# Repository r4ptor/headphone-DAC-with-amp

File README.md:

# Portable headphone DAC with amplifier stage

A simple and portable audio digital to analogue converter with amplifying abilities.

## Structure

The Texas Instruments PCM2707 serves as the USB interface. This interface provides a clock and I2S signal for the main Hifi
digital to analogue converter, the PCM1794A.

Since this converter needs a 3.3V power source a LP5907 ultra-low-noise LDO is being used to
generate the desired voltage.

The DAC provides a differential output current. This is being feeded into a two opamps that are used as transimpedance amplifiers which convert the DAC output current into a differential voltage. Then a difference amplifier converts this differential voltage to single-ended. For this the TI reference design [TIDU672C](http://www.ti.com/litv/pdf/tidu672c) was used. Therefore the Amplifier stage consists as two OPA1612 and a OPA1622.

A LM2662M switched capacitor voltage converter generates the necessary -5V to supply the operational amplifiers with +-5V.

The project is realized with the open source EDA tool [KiCad](https://kicad-pcb.org/).

With the current parts the whole project costs around 45€ at [Digikey](https://www.digikey.com/). For details have a look at the [BOM.csv](https://github.com/r4ptor/headphone-DAC-with-amp/blob/master/BOM.csv) or [BOM.html](https://github.com/r4ptor/headphone-DAC-with-amp/blob/master/BOM.html).

## Datasheets of used components
[PCM2707](https://www.ti.com/lit/ds/symlink/pcm2706.pdf) USB Interface

[PCM1794A](http://www.ti.com/lit/ds/symlink/pcm1794a.pdf) 24-Bit, 192-kHz audio DAC

[LP5907](http://www.ti.com/lit/ds/symlink/lp5907.pdf) Low-noise LDO

[LM2662M](http://www.ti.com/lit/ds/symlink/lm2662.pdf) Voltage converter

[OPA1612](http://www.ti.com/lit/ds/symlink/opa1612.pdf) Operational amplifier

[OPA1622](http://www.ti.com/lit/ds/symlink/opa1622.pdf) Operational amplifier

## Rendered picture of the current PCB layout

Note: old design!

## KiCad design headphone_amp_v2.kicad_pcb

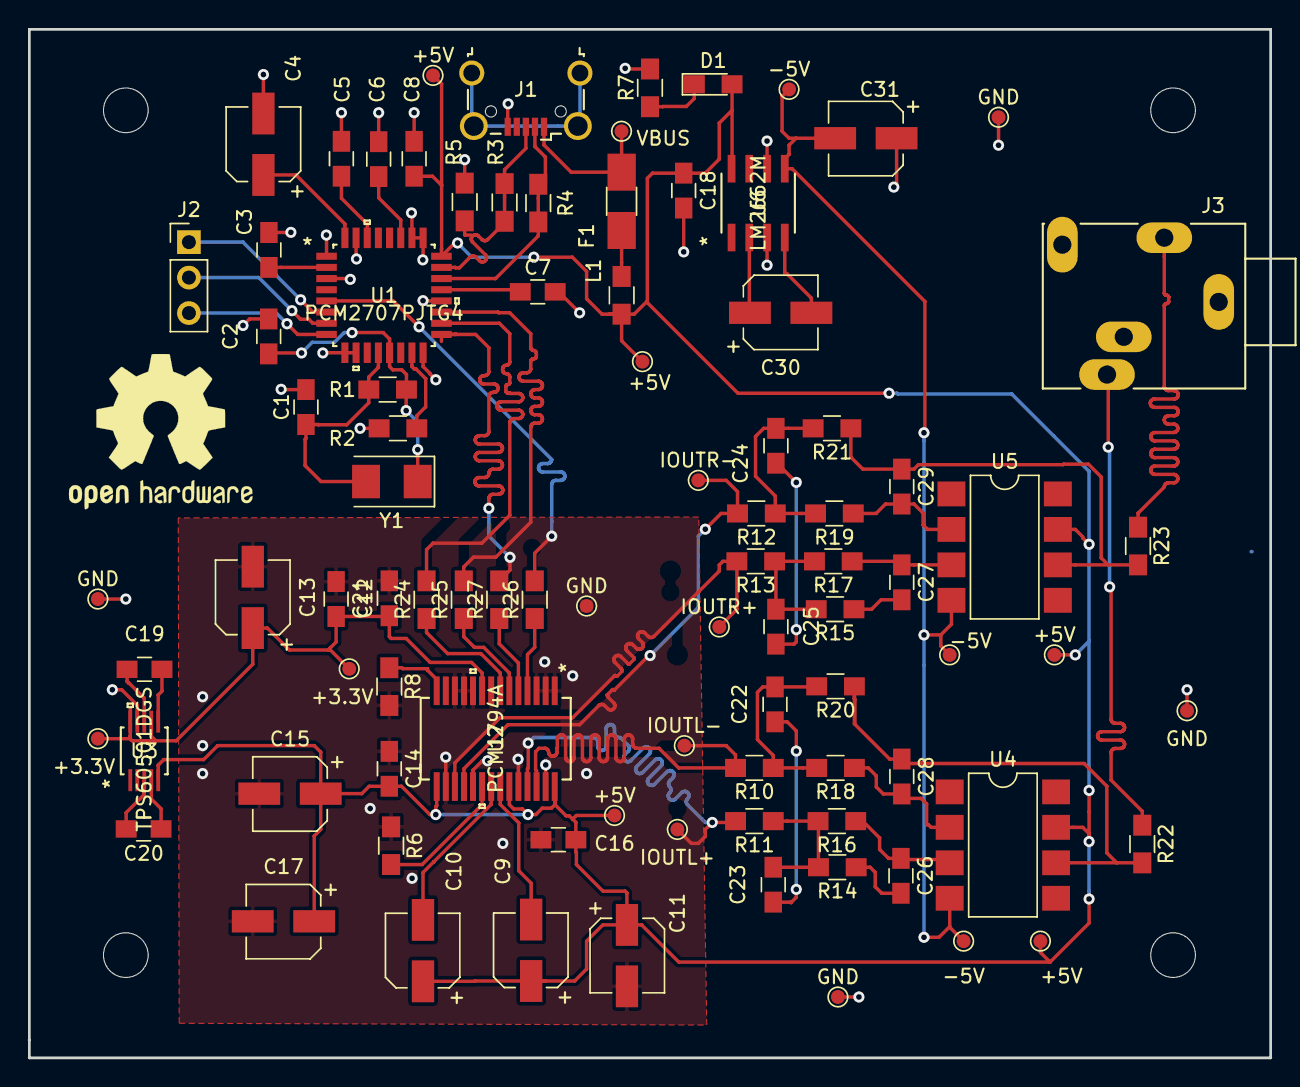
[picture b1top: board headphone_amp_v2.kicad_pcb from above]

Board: 2 copper layers, 88.9 x 73.7 mm, 90 parts (0 on the bottom side), 58 nets.

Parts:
+3.3V, +3.3V#2, +5V, +5V#2, +5V#3, +5V#4, +5V#5: TestPoint_Pad_D1.0mm
-5V, -5V#2, -5V#3: TestPoint_Pad_D1.0mm
C1, C2: 22pF; C_0805_HandSoldering
C3, C5, C6, C7, C8, C19, C20: 1uF; C_0805_HandSoldering
C4, C13: 10uF; CP_Elec_5x5.8
C9, C10, C30, C31: 47uF; CP_Elec_5x5.3
C11, C15, C17: 10uF; CP_Elec_5x5.3
C12, C14, C16: 0.1uF; C_0805_HandSoldering
C18: 2.2uF; C_0805_HandSoldering
C21: 10uF; C_0805_HandSoldering
C22, C23, C24, C25: 4.7nF; C_0805_HandSoldering
C26, C27, C28, C29: 1nF; C_0805_HandSoldering
D1: LED blue; LED_0805_HandSoldering
F1: Polyfuse; Fuse_SMD1206_HandSoldering
GND: TestPoint_Pad_D1.0mm
GND#2, GND#3, GND#4, GND#5: TestPoint_Pad_D1.0mm
IOUTL+: TestPoint_Pad_D1.0mm
IOUTL-: TestPoint_Pad_D1.0mm
IOUTR+: TestPoint_Pad_D1.0mm
IOUTR-: TestPoint_Pad_D1.0mm
J1: USB_OTG; USB_Micro-B_Wuerth-629105150521_CircularHoles
J2: HID_JMP; Pin_Header_Straight_1x03_Pitch2.54mm
J3: AudioJack3_Ground; Stereo_Jack_3.5mm_Switch_Ledino_KB3SPRS
L1: 1A; L_0805_HandSoldering
R1: 1M; R_0805_HandSoldering
R2, R5: 1.5k; R_0805_HandSoldering
R3, R4, R22, R23: 22R; R_0805_HandSoldering
R6, R8: 10k; R_0805_HandSoldering
R7: 560R; R_0805_HandSoldering
R10, R11, R12, R13, R14, R15, R20, R21: 887R; R_0805_HandSoldering
R16, R17, R18, R19: 1.02k; R_0805_HandSoldering
R24, R25, R26: 10R; R_0805_HandSoldering
R27: 47R; R_0805_HandSoldering
U1: PCM2707PJTG4
U2: PCM1794A; PCM1794ADBG4
U3: TPS60501DGS; TPS60501DGSG4
U4, U5: OPA2134PA; SMDIP-8_W7.62mm
U6: LM2662M
VBUS: TestPoint_Pad_D1.0mm
Y1: 12Mhz; Crystal_SMD_5032-2pin_5.0x3.2mm

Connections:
3.3V: +3.3V.1, +3.3V#2.1, C12.1, C13.1, C21.2, U2.9, U3.7, U3.10
5V: +5V.1, +5V#2.1, +5V#3.1, +5V#4.1, +5V#5.1, C8.2, C9.1, C10.1, C11.1, C14.2, C15.1, C16.2, C17.1, C18.1, D1.2, L1.2, U1.24, U2.15, U2.23, U2.28, U3.5, U4.7, U5.7, U6.8
-5V: -5V.1, -5V#2.1, -5V#3.1, C31.2, U4.4, U5.4, U6.5
/D+: J1.3, R3.1, R3.2, R5.2, U1.23
/D-: J1.2, R4.1, R4.2, U1.22
CLK_N: R25.2, U1.19
CLK_P: R24.2, U1.18
DATA_N: R26.2, U1.5
DATA_P: R27.2, U1.17
GND: C1.2, C2.2, C3.2, C4.2, C5.1, C6.1, C7.2, C8.1, C11.2, C12.2, C13.2, C14.1, C15.2, C16.1, C17.2, C18.2, C21.1, C31.1, GND.1, GND#2.1, GND#3.1, GND#4.1, GND#5.1, J1.5, J3.3, R2.2, R5.1, R6.1, R7.2, R8.2, U1.1, U1.3, U1.9, U1.10, U1.16, U1.20, U1.25, U1.26, U1.31, U2.1, U2.2, U2.3, U2.8, U2.10, U2.11, U2.12, U2.16, U2.19, U2.24, U2.27, U3.9, U6.3, U6.6
IOUTL+: IOUTL+.1, R11.2, U2.25
IOUTL-: IOUTL-.1, R10.2, U2.26
IOUTR+: IOUTR+.1, R13.2, U2.17
IOUTR-: IOUTR-.1, R12.2, U2.18
unnamed: C1.1, R1.2, U1.12, Y1.2
unnamed: C2.1, R1.1, U1.13, Y1.1
unnamed: C3.1, U1.2
unnamed: C4.1, U1.32
unnamed: C5.2, U1.30
unnamed: C6.2, U1.27
unnamed: C7.1, U1.21
unnamed: C9.2, U2.22
unnamed: C10.2, U2.21
unnamed: C19.1, U3.6
unnamed: C19.2, U3.8
unnamed: C20.1, U3.4
unnamed: C20.2, U3.3
unnamed: C22.1, R10.1, R18.2, R20.2
unnamed: C22.2, C23.1
unnamed: C23.2, R11.1, R14.2, R16.2
unnamed: C24.1, R12.1, R19.2, R21.2
unnamed: C24.2, C25.1
unnamed: C25.2, R13.1, R15.2, R17.2
unnamed: C26.1, R16.1, U4.3
unnamed: C26.2, R14.1
unnamed: C27.1, R17.1, U5.3
unnamed: C27.2, R15.1
unnamed: C28.1, R20.1, R22.2, U4.6
unnamed: C28.2, R18.1, U4.2
unnamed: C29.1, R21.1, R23.2, U5.6
unnamed: C29.2, R19.1, U5.2
unnamed: C30.1, U6.2
unnamed: C30.2, U6.4
unnamed: D1.1, R7.1
unnamed: F1.1, J1.1, VBUS.3
unnamed: F1.2, L1.1
unnamed: J2.1, U1.6
unnamed: J2.2, U1.7
unnamed: J2.3, U1.8
unnamed: R2.1, U1.15
unnamed: R6.2, U2.20
unnamed: R8.1, U2.14
unnamed: R24.1, U2.7
unnamed: R25.1, U2.6
unnamed: R26.1, U2.4
unnamed: R27.1, U2.5
OUTL: J3.2, R22.1
OUTR: J3.1, R23.1

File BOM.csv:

Component,Description,Part,References,Value,Footprint,Quantity Per PCB,Datasheet,Part number,Note
1,Unpolarized capacitor,C,C12 C14 C16,0.1uF,C_0805_HandSoldering,3,http://media.digikey.com/pdf/Data%20Sheets/Samsung%20PDFs/CL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,CL21F104ZBCNNNC,
2,Polarised capacitor,CP1,C4 C11 C13 C15 C17,10uF,CP_Elec_5x5.8,5,https://industrial.panasonic.com/cdbs/www-data/pdf/RDE0000/A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,EEE-1VA100SR,
3,Unpolarized capacitor,C,C21,10uF,C_0805_HandSoldering,1,http://www.samsungsem.com/kr/support/product-search/mlcc/CL2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,CL21A106KPFNNNG,
4,Unpolarized capacitor,C,C26 C27 C28 C29,1nF,C_0805_HandSoldering,4,http://www.samsungsem.com/kr/support/product-search/mlcc/CL2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,CL21C010CBANNNC,
5,Unpolarized capacitor,C,C3 C5 C6 C7 C8 C19 C20,1uF,C_0805_HandSoldering,7,http://www.yageo.com/documents/recent/UPY-GPHC_X7R_6.3V-to-5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,CC0805KKX7R6BB105,
6,Unpolarized capacitor,C,C18,2.2uF,C_0805_HandSoldering,1,https://api.kemet.com/component-edge/download/datasheet/C080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,C0805C225K8RACTU,
7,Unpolarized capacitor,C,C1 C2,22pF,C_0805_HandSoldering,2,https://4donline.ihs.com/images/VipMasterIC/IC/AVXC/AVXC-S-A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,08051A220KAT2A,
8,Unpolarized capacitor,C,C22 C23 C24 C25,4.7nF,C_0805_HandSoldering,4,https://api.kemet.com/component-edge/download/datasheet/C080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,C0805C472KARECAUTO,
9,Polarised capacitor,CP1,C9 C10 C30 C31,47uF,CP_Elec_5x5.3,4,https://industrial.panasonic.com/cdbs/www-data/pdf/RDE0000/A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,EEE-1CA470WR,Low ESR
10,LED generic,LED,D1,LED blue,LED_0805_HandSoldering,1,http://optoelectronics.liteon.com/upload/download/DS-22-99-0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,LTST-C170TBKT,
11,"resettable fuse, polymeric positive temperature coefficient (PPTC)",Polyfuse,F1,Polyfuse,Fuse_SMD1206_HandSoldering,1,https://belfuse.com/resources/datasheets/circuitprotection/d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,0685T2500-01,
12,"Audio Jack, 3 Poles (Stereo / TRS), Grounded Sleeve",AudioJack3_Ground,J3,AudioJack3_Ground,Stereo_Jack_3.5mm_Switch_Ledino_KB3SPRS,1,https://www.cui.com/product/resource/digikeypdf/sj1-352xn_se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,,
13,"Generic connector, single row, 01x03, script generated (kicad-library-utils/schlib/autogen/connector/)",Conn_01x03_Male,J2,HID_JMP,Pin_Header_Straight_1x03_Pitch2.54mm,1,~,SJ1-3523N,
14,USB mini/micro connector,USB_OTG,J1,USB_OTG,USB_Micro-B_Wuerth-629105150521_CircularHoles,1,https://katalog.we-online.de/em/datasheet/629105150521.pdf,629105150521,
15,Ferrite bead,Ferrite_Bead,L1,1A,L_0805_HandSoldering,1,http://ds.yuden.co.jp/TYCOMPAS/ut/detail.do?productNo=BK2125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,BK2125HS470-T,
16,Resistor,R,R16 R17 R18 R19,1.02k,R_0805_HandSoldering,4,https://industrial.panasonic.com/cdbs/www-data/pdf/RDM0000/A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,ERA-6AEB1021V,
17,Resistor,R,R2 R5,1.5k,R_0805_HandSoldering,2,https://www.seielect.com/Catalog/SEI-rncp.pdf,RNCP0805FTD1K50,
18,Resistor,R,R24 R25 R26,10R,R_0805_HandSoldering,3,https://www.seielect.com/Catalog/SEI-rncp.pdf,RNCP0805FTD10R0,
19,Resistor,R,R6 R8,10k,R_0805_HandSoldering,2,https://www.seielect.com/Catalog/SEI-RNCF.pdf,RNCF0805DTE10K0,
20,Resistor,R,R1,1M,R_0805_HandSoldering,1,https://industrial.panasonic.com/cdbs/www-data/pdf/RDM0000/A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,ERA-6AEB105V,
21,Resistor,R,R3 R4 R22 R23,22R,R_0805_HandSoldering,4,http://www.yageo.com/documents/recent/PYu-RC_Group_51_RoHS_L_9.pdf,RC0805FR-0722RL,
22,Resistor,R,R27,47R,R_0805_HandSoldering,1,https://industrial.panasonic.com/cdbs/www-data/pdf/RDA0000/A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,ERJ-6ENF47R0V,
23,Resistor,R,R7,560R,R_0805_HandSoldering,1,https://www.seielect.com/Catalog/SEI-RMCF_RMCP.pdf,RMCF0805JT560R,
24,Resistor,R,R10 R11 R12 R13 R14 R15 R20 R21,887R,R_0805_HandSoldering,8,http://www.yageo.com/documents/recent/PYu-RC_Group_51_RoHS_L_9.pdf,RC0805FR-07887RL,
25,,LM2662M,U6,LM2662M,LM2662M,1,http://www.ti.com/lit/ds/symlink/lm2662.pdf,LM2662M/NOPB,
26,,OPA2134PA,U4 U5,OPA2134PA,SMDIP-8_W7.62mm,2,http://www.ti.com/lit/ds/symlink/opa2134.pdf,OPA2134PA,
27,"24-Bit, 192-kHz Sampling, Advanced Segment, Audio Stereo Digital-to-Analog Converter, HW Control, SSOP-28",PCM1794A,U2,PCM1794A,PCM1794ADBG4,1,http://www.ti.com/lit/ds/symlink/pcm1794a.pdf,PCM1794ADBR,
28,,PCM2707PJTG4,U1,PCM2707PJTG4,PCM2707PJTG4,1,http://www.ti.com/lit/ds/symlink/pcm2706.pdf,PCM2707CPJT,
29,"250mA High-Efficiency Step-Down Charge Pump Regulator, 3.3V Output Voltage, MSOP-10",TPS60501DGS,U3,TPS60501DGS,TPS60501DGSG4,1,http://www.ti.com/lit/ds/symlink/tps60503.pdf,TPS60501DGSR,
30,Two pin crystal,Crystal,Y1,12Mhz,Crystal_SMD_5032-2pin_5.0x3.2mm,1,https://media.digikey.com/pdf/Data%20Sheets/AVX%20PDFs/CX503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,CX5032GB12000H0PESZZ,





Component Groups:,30
Component Count:,70
Fitted Components:,70
Number of PCBs:,1
Total components:,70
Schematic Version:,0.2
Schematic Date:,2018-09-20
BoM Date:,23/09/2018 17:00:56
Schematic Source:,F:\nextcloud\eagle_projects\headphone_dac_with_amp_v2\headphone_amp_v2.sch
KiCad Version:,Eeschema (5.0.0)

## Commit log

2018-09-22 initial commit, schematic done, datasheets can be found within the kicad symbols
2018-09-22 a first version of the layouted board. Not the prettiest but 0 errors in DRC. Raytraced 3D image included
2018-09-22 updated README.me. Added project description and links to datasheets
2018-09-22 README.md fixed formatting
2018-09-22 added raytraced picture to the readme
2018-09-22 added todolist to the readme
2018-09-22 fixed formatting in the readme...duh...
2018-09-22 updated the layout of components and rerouted the traces. The components are grouped more nicely, the board length was reduced by 5mm
2018-09-22 added mountingholes(m3)
2018-09-22 updated the opamps and crystal to a smd version, removed ground traces in favor of vias
2018-09-22 added a pcb of the schematic and overview pictures
2018-09-22 PCB: Draft update with better component placement
    This moves some components around to reduce via count, improve bypass capacitor layout, and improve manufacturability.
    Additional work needs to be done to clean up the positioning of refdes, duplicate the left audio channel layout.
2018-09-22 added testpads[to be routed], updated rendered images
2018-09-23 updated board layout as suggested by the reddit community. New rendered pictures added. Polyfuse for VBUS added
2018-09-23 updated the pictes(silkscreen changed with open hardware logo
2018-09-23 minor changes, HMTL BOM created
2018-09-23 fixed some footprints, inserted all needed specification sheets, updated the BOM list
2018-09-23 updated fuse footprint
2018-09-23 added several testpoints and moved some silkscreen component names for visibility
2018-09-24 length matched the signal traces
2018-09-24 updated the rendered pictures
2018-09-24 updated BOM, generated a *.csv and *.html version. Updated the readme with the total cost
2018-09-24 fixed a typo
2018-09-25 fixed a too narrow track to J2
2018-10-25 first draft of the schematic isnt't working. New draft got updated with a different 3.3V converter and different amplifier stage. Amp stag now uses OPA1612 and OPA1622. Amp stage ref design is being 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
2018-10-25 fixed LDO link
2018-10-25 added all desired values to the compoments

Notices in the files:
parts and their libraries:
Copyright 2016 Accelerated Designs. All rights reserved.
